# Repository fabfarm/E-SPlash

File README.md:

# FabLab Irrigation System

## Design

C++ for a Microprocessor that includes an embedded http server.

The http server displays controls for N zones, where each zone has:

- turn on time
- turn on duration

```
Valve1 \
Valve2  --- Microprocessor <==> Web Interface  
ValveN /
```

## Web server methods

| **Endpoint** | **Purpose**       |
|--------------|-------------------|
| /getData     | returns json      |
| /updateData  | gets updated json |

## Core Logic

1) start with our json object.
2) we get new data (temp/humidit/y/relay status)
3) update the json object
4) serialize ==> json
5) return json to html

**State Problem**  
When the microcontroller loses power, we lose state. We therefore need to persist settings to disk.

- Settings are *read* from disk on startup
- Settings are *saved* each time a user changes settings in the web ui
- Settings are kept in memory and we check against them

Psuedo code:
```
Startup: 
  - read json to doc obj
  - init wifi
  - init http server

/getData
  - serialize doc obj to Json
  - return Json to caller
  - no logic

/updateData 
  - take incoming Json and save it to disk
  - arduinoJson magically serializes incoming request to our doc object for free
  - no logic 

Loop (no disk i/o):
  - examine current state of in memory doc object and take action
```

## Data format

```json
{
    "data": {
        "currentTime": "Tuesday, June 23 2020 11:54:16",
        "temperature": "29.90",
        "humidity": "51.00",
        "override": 0,
        "ssid": "myssid",
        "pass": "my password"
    },
    "relays": [
        {
            "name": "Fruit Tree",
            "pin": 25,
            "isRunning": 1,
            "isEnabled": 0,
            "times": [
                {
                    "startTime": "03:00",
                    "duration": "0"
                }
            ]
        },
        {
            "name": "Vegie Garden",
            "pin": 26,
            "isRunning": 1,
            "isEnabled": 0,
            "status": 1,
            "times": [
                {
                    "startTime": "12:00",
                    "duration": "0"
                },
                {
                    "startTime": "12:30",
                    "duration": "0"
                }
            ]
        },
        {
            "name": "Cypress Hill",
            "pin": 33,
            "isRunning": 1,
            "isEnabled": 0,
            "status": 1,
            "times": [
                {
                    "startTime": "12:45",
                    "duration": "0"
                },
                {
                    "startTime": "10:00",
                    "duration": "0"
                },
                {
                    "startTime": "16:45",
                    "duration": "0"
                }
            ]
        }
    ]
}

```

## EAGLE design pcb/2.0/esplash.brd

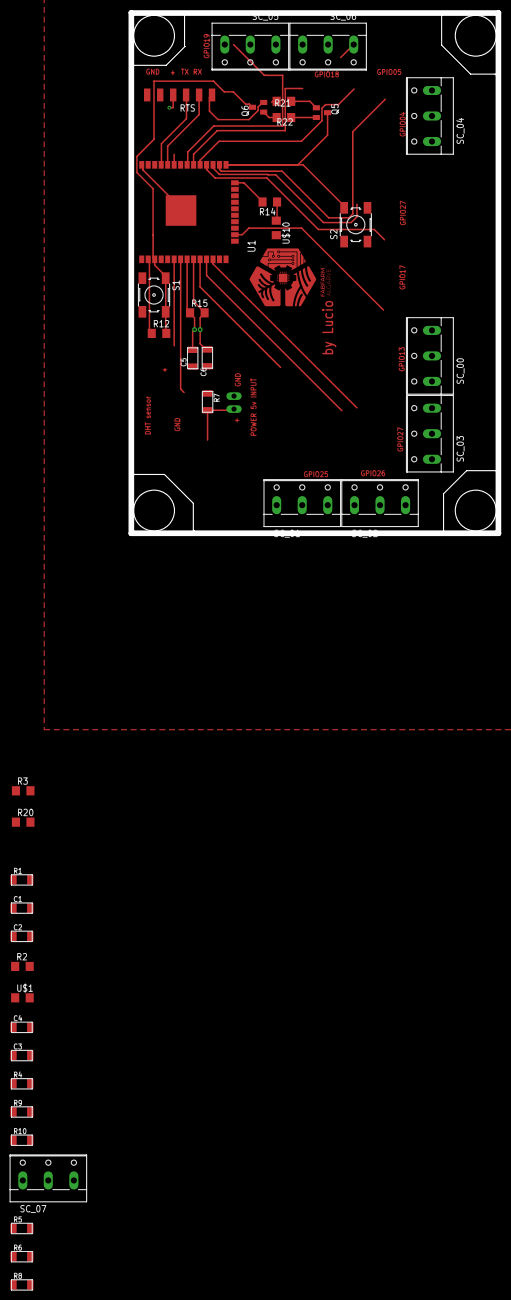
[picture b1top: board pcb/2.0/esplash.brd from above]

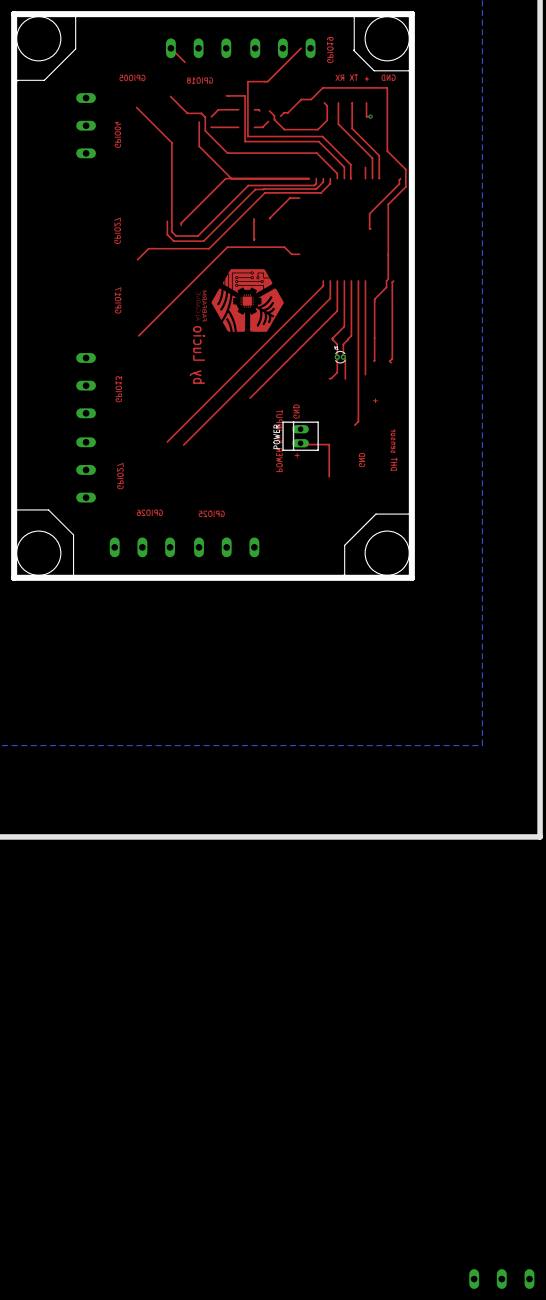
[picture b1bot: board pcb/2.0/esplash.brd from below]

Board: 2 copper layers, 72.0 x 102.0 mm, 40 parts (2 on the bottom side), 31 nets.

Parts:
C1: 10uF; C1206FAB
C2: 100nF; C1206FAB
C3, C4: 1uF; C1206FAB
C5, C6: 15pf; C1206FAB
POWER: 22-23-2021
Q5, Q6: BCX70SMD; SOT23
R1, R6, R8: 10Kohm; R1206FAB
R2, R14: 100ohm; R1206
R3, R20: 50 ohm; R1206
R4: 100Kohm; R1206FAB
R5: 4.9Kohm; R1206FAB
R7: 49.9Kohm; R1206FAB
R9: 50Kohm; R1206FAB
R10: 5Kohm; R1206FAB
R12, R21, R22: 10k; R1206
R15: 5M; R1206
RTS: FTDI-SMD-HEADER; 1X06SMD
S1: Reset; 6MM_SWITCH
S2: GPIO0 Button; 6MM_SWITCH
SC_00, SC_01, SC_02, SC_03, SC_04, SC_05, SC_06, SC_07: SC; W237-103
U1: ESP-WROOM-32
U$1, U$10: LED; LED1206
Y1: ECS-.327-12.5-13X; XTAL_ECS-.327-12.5-13X

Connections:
3V3: C1.2, C2.1, C3.1, R2.2, R12.1, U1.2
32K_XN: C6.2, R15.2, U1.9, Y1.1
32K_XP: C5.2, R15.1, U1.8, Y1.2
BUT_CHIP_LO: R20.1, S1.3, S1.4
BUT_IO0_LO: R3.1, S2.3, S2.4
CHIP_PU: C4.1, Q6.3, R12.2, S1.1, S1.2, U1.3
DTR: Q5.2, R22.2
GND: C1.1, C2.2, C3.2, C4.2, C5.1, C6.1, POWER.2, R1.1, R3.2, R20.2, RTS.1, SC_00.1, SC_01.1, SC_02.1, SC_03.1, SC_04.1, SC_05.1, SC_06.1, SC_07.1, U1.1, U1.15, U1.38, U1.GND, U$1.2, U$10.2
GPIO0: Q5.3, S2.1, S2.2, U1.25
GPIO1/TXD0: RTS.4, U1.35
GPIO02: R14.2, U1.24
GPIO3/RXD0: RTS.5, U1.34
GPIO4/POWER_VOLT_IN: R1.2, R10.1, U1.26
GPIO12/BATT_IN_7: SC_06.3, U1.14
GPIO13/BATT_IN_8: SC_07.3, U1.16
GPIO14/BATT_IN_6: SC_05.3, U1.13
GPIO25/BATT_IN_3: SC_02.3, U1.10
GPIO26/BATT_IN_4: SC_03.3, U1.11
GPIO27/BATT_IN_5: SC_04.3, U1.12
GPIO34/BATT_IN_1: SC_00.3, U1.6
GPIO35/BATT_IN_2: SC_01.3, U1.7
unnamed: R2.1, U$1.1
unnamed: R4.2, R7.1, R9.2
unnamed: R4.1, R9.1, R10.2
unnamed: R5.1, R6.2
unnamed: R6.1, R8.2
unnamed: R14.1, U$10.1
unnamed: Q5.1, R21.1
unnamed: Q6.1, R22.1
RTS: Q6.2, R21.2, RTS.6
VCC: POWER.1, R7.2, RTS.3, SC_00.2, SC_01.2, SC_02.2, SC_03.2, SC_04.2, SC_05.2, SC_06.2, SC_07.2

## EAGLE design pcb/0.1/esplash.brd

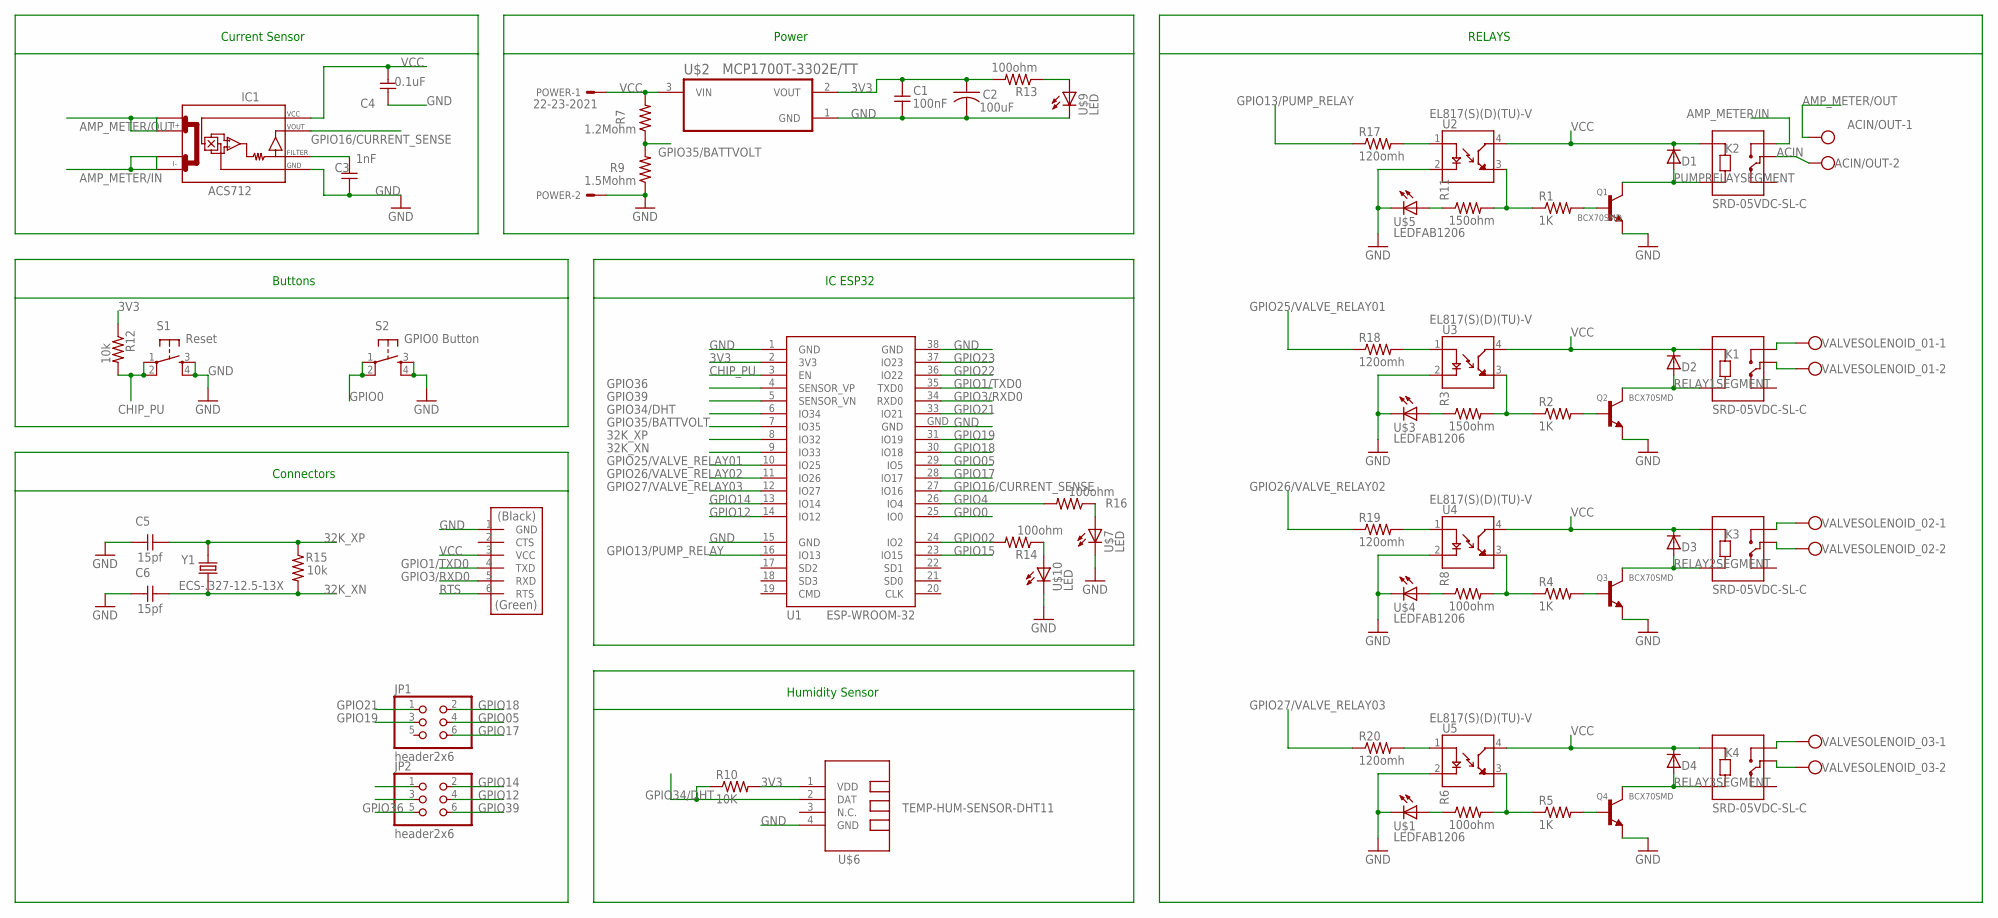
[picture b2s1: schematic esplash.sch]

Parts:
ACIN/OUT: W237-102
C1: 100nF; C1206FAB
C2: 100uF; C1206FAB
C3: 1nF; C1206FAB
C4: 0.1uF; C1206FAB
C5, C6: 15pf; C1206FAB
D1, D2, D3, D4: DIODESOD123; SOD123
IC1: ACS712; SO08
JP1, JP2: header2x6; 2X03
K1, K2, K3, K4: SRD-05VDC-SL-C; RELAY_SRD-05VDC-SL-C
POWER: 22-23-2021
Q1, Q2, Q3, Q4: BCX70SMD; SOT23
R1, R2, R4, R5: 1K; R1206FAB
R3, R11: 150ohm; R1206FAB
R6, R8: 100ohm; R1206FAB
R7: 1.2Mohm; R1206FAB
R9: 1.5Mohm; R1206FAB
R10: 10K; R1206FAB
R12, R15: 10k; R1206
R13, R14, R16: 100ohm; R1206
R17, R18, R19, R20: 120omh; R1206FAB
RTS: FTDI-SMD-HEADER; 1X06SMD
S1: Reset; 6MM_SWITCH
S2: GPIO0 Button; 6MM_SWITCH
U1: ESP-WROOM-32
U2, U3, U4, U5: EL817(S)(D)(TU)-V; SOIC254P1030X460-4N
U$1, U$3, U$4, U$5: LEDFAB1206; LED1206FAB
U$2: MCP1700T-3302E/TT; SOT95P237X112-3N
U$6: TEMP-HUM-SENSOR-DHT11
U$7, U$9, U$10: LED; LED1206
VALVESOLENOID_01, VALVESOLENOID_02, VALVESOLENOID_03: W237-102
Y1: ECS-.327-12.5-13X; XTAL_ECS-.327-12.5-13X

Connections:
3V3: C1.2, C2.1, R10.2, R12.1, R13.2, U1.2 (3V3), U$2.2 (VOUT), U$6.1 (VDD)
32K_XN: C6.2, R15.2, U1.9 (IO33), Y1.1
32K_XP: C5.2, R15.1, U1.8 (IO32), Y1.2
ACIN: ACIN/OUT.2, K2.COM
AMP_METER/IN: IC1.3 (I-_0), IC1.4 (I-_1), K2.NO
AMP_METER/OUT: ACIN/OUT.1, IC1.1 (I+_0), IC1.2 (I+_1)
CHIP_PU: R12.2, S1.1, S1.2 (P1), U1.3 (EN)
DELETE: C3.2, IC1.6 (FILTER)
GND: C1.1, C2.2, C3.1, C4.1, C5.1, C6.1, IC1.5 (GND), POWER.2, Q1.2 (E), Q2.2 (E), Q3.2 (E), Q4.2 (E), R9.1, RTS.1 (GND), S1.3 (S), S1.4 (S1), S2.3 (S), S2.4 (S1), U1.1 (GND), U1.15 (GND), U1.38 (GND), U1.GND, U2.2 (C), U3.2 (C), U4.2 (C), U5.2 (C), U$1.2 (C), U$2.1 (GND), U$3.2 (C), U$4.2 (C), U$5.2 (C), U$6.4 (GND), U$7.2 (C), U$9.2 (C), U$10.2 (C)
GPIO0: S2.1, S2.2 (P1), U1.25 (IO0)
GPIO1/TXD0: RTS.4 (TXD), U1.35 (TXD0)
GPIO02: R14.2, U1.24 (IO2)
GPIO3/RXD0: RTS.5 (RXD), U1.34 (RXD0)
GPIO4: R16.2, U1.26 (IO4)
GPIO05: JP1.4, U1.29 (IO5)
GPIO12: JP2.4, U1.14 (IO12)
GPIO13/PUMP_RELAY: R17.1, U1.16 (IO13)
GPIO14: JP2.2, U1.13 (IO14)
GPIO15: U1.23 (IO15)
GPIO16/CURRENT_SENSE: IC1.7 (VOUT), U1.27 (IO16)
GPIO17: JP1.6, U1.28 (IO17)
GPIO18: JP1.2, U1.30 (IO18)
GPIO19: JP1.3, U1.31 (IO19)
GPIO21: JP1.1, U1.33 (IO21)
GPIO22: U1.36 (IO22)
GPIO23: U1.37 (IO23)
GPIO25/VALVE_RELAY01: R18.1, U1.10 (IO25)
GPIO26/VALVE_RELAY02: R19.1, U1.11 (IO26)
GPIO27/VALVE_RELAY03: R20.1, U1.12 (IO27)
GPIO34/DHT: R10.1, U1.6 (IO34), U$6.2 (DAT)
GPIO35/BATTVOLT: R7.1, R9.2, U1.7 (IO35)
GPIO36: JP2.5, U1.4 (SENSOR_VP)
GPIO39: JP2.6, U1.5 (SENSOR_VN)
unnamed: R1.1, R11.2, U2.3 (ET)
unnamed: K1.COM, VALVESOLENOID_01.2
unnamed: Q2.1 (B), R2.2
unnamed: R11.1, U$5.1 (A)
unnamed: R14.1, U$10.1 (A)
unnamed: K1.NO, VALVESOLENOID_01.1
unnamed: R3.1, U$3.1 (A)
unnamed: R2.1, R3.2, U3.3 (ET)
unnamed: K3.COM, VALVESOLENOID_02.2
unnamed: Q3.1 (B), R4.2
unnamed: R8.1, U$4.1 (A)
unnamed: R4.1, R8.2, U4.3 (ET)
unnamed: K3.NO, VALVESOLENOID_02.1
unnamed: K4.COM, VALVESOLENOID_03.2
unnamed: Q4.1 (B), R5.2
unnamed: R6.1, U$1.1 (A)
unnamed: R5.1, R6.2, U5.3 (ET)
unnamed: K4.NO, VALVESOLENOID_03.1
unnamed: R13.1, U$9.1 (A)
unnamed: R16.1, U$7.1 (A)
unnamed: R17.2, U2.1 (A)
unnamed: R18.2, U3.1 (A)
unnamed: R19.2, U4.1 (A)
unnamed: R20.2, U5.1 (A)
unnamed: Q1.1 (B), R1.2
PUMPRELAYSEGMENT: D1.ANODE (A), K2.A2, Q1.3 (C)
RELAY1SEGMENT: D2.ANODE (A), K1.A2, Q2.3 (C)
RELAY2SEGMENT: D3.ANODE (A), K3.A2, Q3.3 (C)
RELAY3SEGMENT: D4.ANODE (A), K4.A2, Q4.3 (C)
RTS: RTS.6 (RTS)
VCC: C4.2, D1.CATHODE (C), D2.CATHODE (C), D3.CATHODE (C), D4.CATHODE (C), IC1.8 (VCC), K1.A1, K2.A1, K3.A1, K4.A1, POWER.1, R7.2, RTS.3 (VCC), U2.4 (CT), U3.4 (CT), U4.4 (CT), U5.4 (CT), U$2.3 (VIN)

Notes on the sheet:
RELAYS
Power
IC ESP32
Humidity Sensor
Current Sensor
Buttons
Connectors

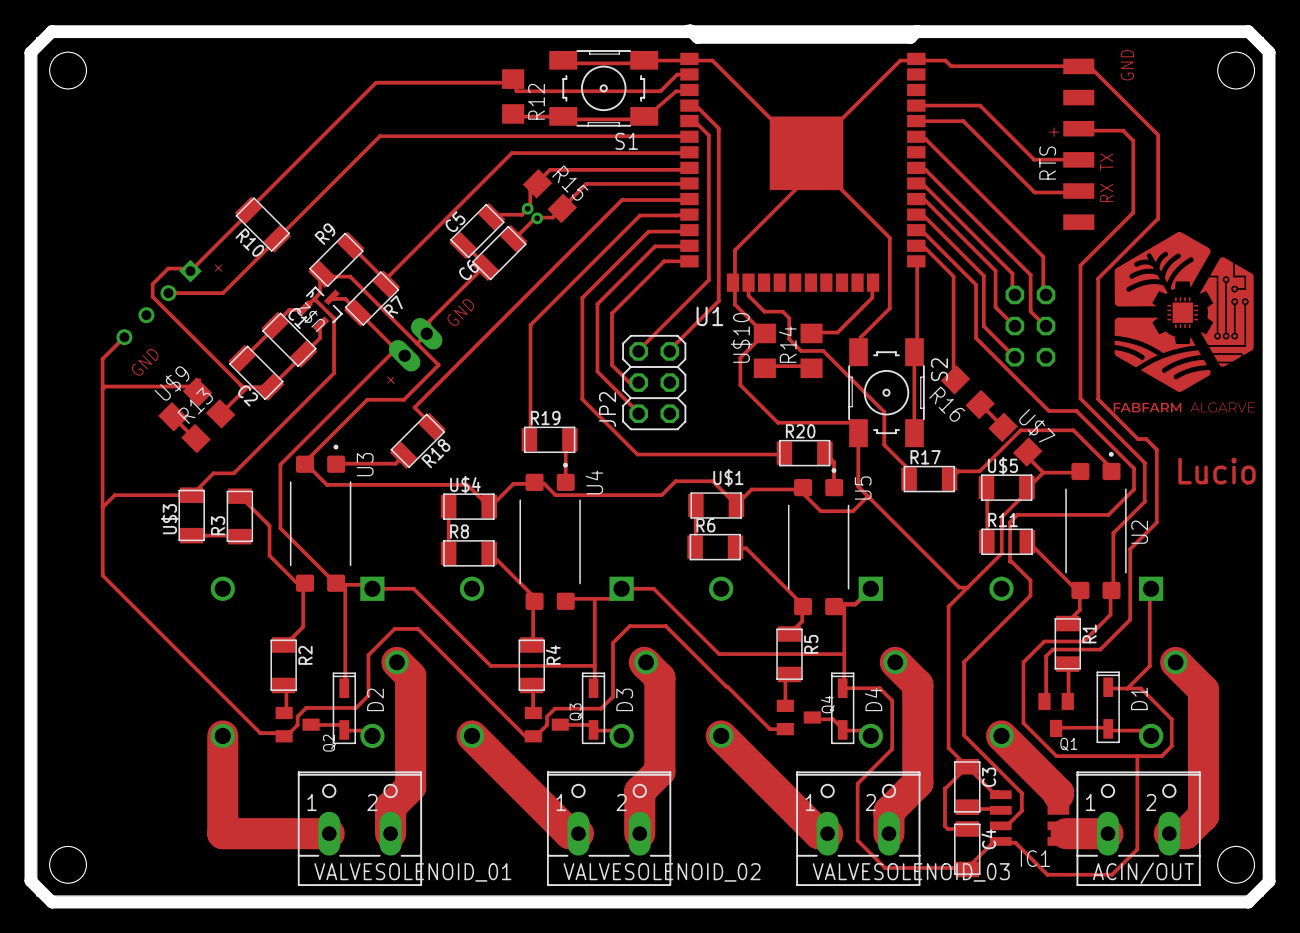
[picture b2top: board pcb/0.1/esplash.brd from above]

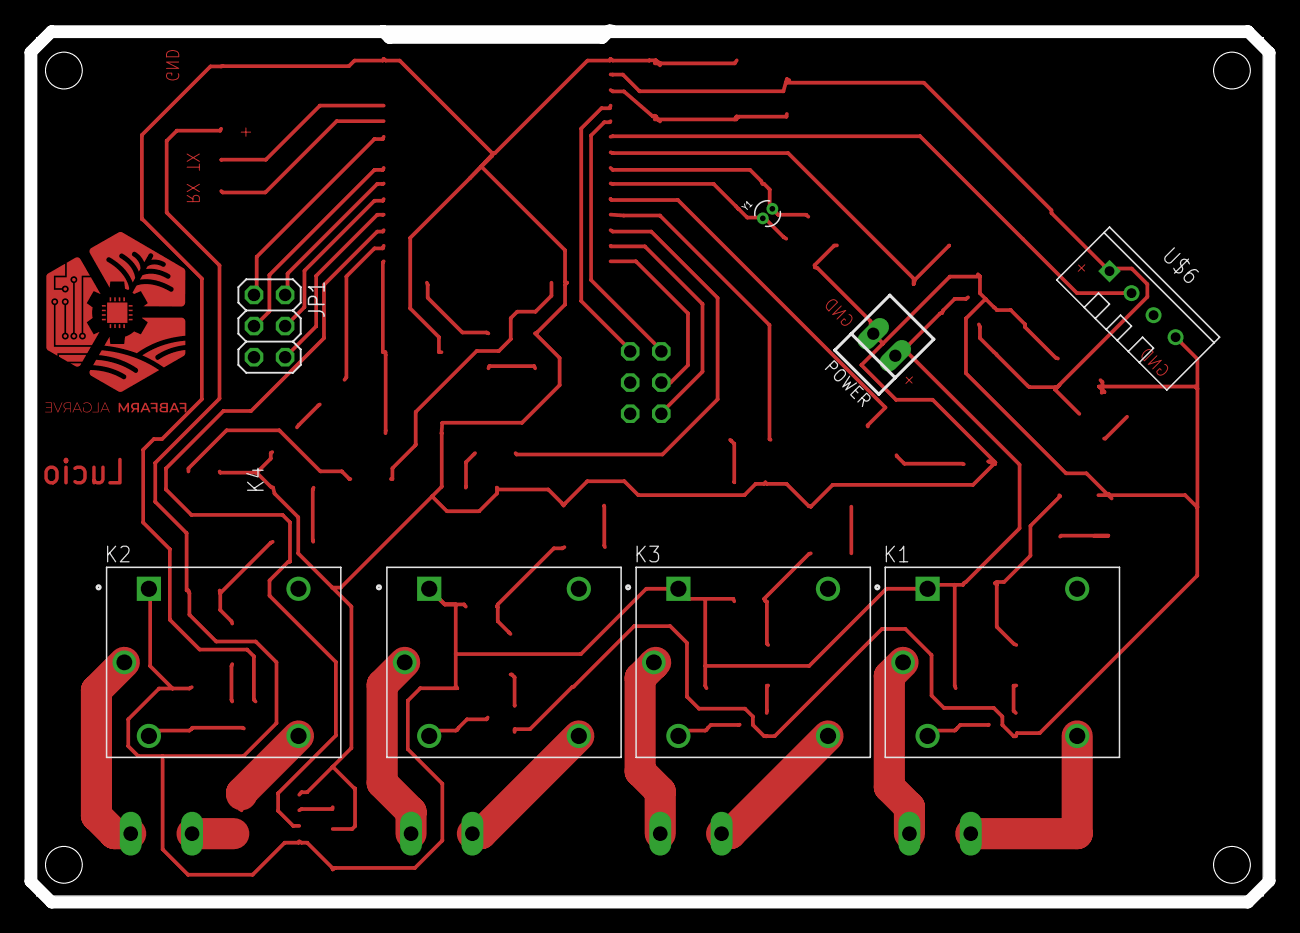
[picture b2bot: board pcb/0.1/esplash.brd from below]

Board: 2 copper layers, 101.0 x 71.0 mm, 64 parts (8 on the bottom side), 60 nets.

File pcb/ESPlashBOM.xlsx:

Part | Value | Device | Package | Description | ARROW_AMERICAS-PURCHASE-URL | AVAILABILITY | DESCRIPTION.1 | DIGIKEY-PURCHASE-URL | MF | MOUSER-PURCHASE-URL | MP | MPN | OC_FARNELL | OC_NEWARK | PACKAGE.1 | POPULARITY | PRICE | Column1
POWER | 22-23-2021 | 22-23-2021 | 22-23-2021 | .100 (2.54mm) Center Header - 2 Pin" |  |  |  |  | MOLEX |  |  | 22-23-2021 | 1462926 | 25C3832 |  | 40
S2 | GPIO0 Button | 6MM_SWITCH6MM_SWITCH | 6MM_SWITCH | OMRON SWITCH
S1 | Reset | 6MM_SWITCH6MM_SWITCH | 6MM_SWITCH | OMRON SWITCH
IC1 | ACS712 | ACS712 | SO08
Q1 | BCX70SMD | BCX70SMD | SOT23 | NPN TRANSISTOR |  |  |  |  |  |  |  |  |  |  |  | 0
Q2 | BCX70SMD | BCX70SMD | SOT23 | NPN TRANSISTOR |  |  |  |  |  |  |  |  |  |  |  | 0
Q3 | BCX70SMD | BCX70SMD | SOT23 | NPN TRANSISTOR |  |  |  |  |  |  |  |  |  |  |  | 0
Q4 | BCX70SMD | BCX70SMD | SOT23 | NPN TRANSISTOR |  |  |  |  |  |  |  |  |  |  |  | 0
C4 | 0.1uF | CAP-UNPOLARIZEDFAB | C1206FAB
C1 | 100nF | CAP-UNPOLARIZEDFAB | C1206FAB
C5 | 15pf | CAP-UNPOLARIZEDFAB | C1206FAB
C6 | 15pf | CAP-UNPOLARIZEDFAB | C1206FAB
C3 | 1nF | CAP-UNPOLARIZEDFAB | C1206FAB
C2 | 100uF | CAP-US1206FAB | C1206FAB
D1 |  | DIODESOD123 | SOD123 | DIODE
D2 |  | DIODESOD123 | SOD123 | DIODE
D3 |  | DIODESOD123 | SOD123 | DIODE
D4 |  | DIODESOD123 | SOD123 | DIODE
Y1 | ECS-.327-12.5-13X | ECS-.327-12.5-13X | XTAL_ECS-.327-12.5-13X | Crystal Cylindrical Can, Radial |  | Unavailable | 32.768kHz Â±20ppm Crystal 12.5pF 35 kOhms Cylindrical Can, Radial |  | ECS Inc. |  | ECS-.327-12.5-13X |  |  |  | Cylindrical Can Radial ECS International |  | None
U2 | EL817(S)(D)(TU)-V | EL817(S)(D)(TU)-V | SOIC254P1030X460-4N | Optocoupler DC-IN 1-CH Transistor DC-OUT 4-Pin PDIP Tube |  | Unavailable | Optoisolator Transistor Output 5000Vrms 1 Channel 4-SMD |  | Everlight Electronics |  | EL817(S)(D)(TU)-V |  |  |  | SMD-4 Everlight |  | None
U3 | EL817(S)(D)(TU)-V | EL817(S)(D)(TU)-V | SOIC254P1030X460-4N | Optocoupler DC-IN 1-CH Transistor DC-OUT 4-Pin PDIP Tube |  | Unavailable | Optoisolator Transistor Output 5000Vrms 1 Channel 4-SMD |  | Everlight Electronics |  | EL817(S)(D)(TU)-V |  |  |  | SMD-4 Everlight |  | None
U4 | EL817(S)(D)(TU)-V | EL817(S)(D)(TU)-V | SOIC254P1030X460-4N | Optocoupler DC-IN 1-CH Transistor DC-OUT 4-Pin PDIP Tube |  | Unavailable | Optoisolator Transistor Output 5000Vrms 1 Channel 4-SMD |  | Everlight Electronics |  | EL817(S)(D)(TU)-V |  |  |  | SMD-4 Everlight |  | None
U5 | EL817(S)(D)(TU)-V | EL817(S)(D)(TU)-V | SOIC254P1030X460-4N | Optocoupler DC-IN 1-CH Transistor DC-OUT 4-Pin PDIP Tube |  | Unavailable | Optoisolator Transistor Output 5000Vrms 1 Channel 4-SMD |  | Everlight Electronics |  | EL817(S)(D)(TU)-V |  |  |  | SMD-4 Everlight |  | None
U1 | ESP-WROOM-32 | ESP-WROOM-32 | ESP-WROOM-32 | Espressif Systems ESP-WROOM-32
RTS | FTDI-SMD-HEADER | FTDI-SMD-HEADER | 1X06SMD
U$7 | LED | LED | LED1206 | LED
U$9 | LED | LED | LED1206 | LED
U$10 | LED | LED | LED1206 | LED
U$1 | LEDFAB1206 | LEDFAB1206 | LED1206FAB | LED
U$3 | LEDFAB1206 | LEDFAB1206 | LED1206FAB | LED
U$4 | LEDFAB1206 | LEDFAB1206 | LED1206FAB | LED
U$5 | LEDFAB1206 | LEDFAB1206 | LED1206FAB | LED
U$2 | MCP1700T-3302E/TT | MCP1700T-3302E/TT | SOT95P237X112-3N |  | https://snapeda.com/shop?store=Arrow+Americas&id=4791194 | Unavailable | IC REG LINEAR 3.3V 250MA SOT23-3 | https://snapeda.com/shop?store=DigiKey&id=4791194 | Microchip Technology | https://snapeda.com/shop?store=Mouser&id=4791194 | MCP1700T-3302E/TT |  |  |  | None |  | None
JP1 | header2x6 | PINHD-2X3 | 2X03 | PIN HEADER |  |  |  |  |  |  |  |  |  |  |  | 62
JP2 | header2x6 | PINHD-2X3 | 2X03 | PIN HEADER |  |  |  |  |  |  |  |  |  |  |  | 62
R13 | 100ohm | RES-US1206 | R1206 | Resistor (US Symbol)
R14 | 100ohm | RES-US1206 | R1206 | Resistor (US Symbol)
R16 | 100ohm | RES-US1206 | R1206 | Resistor (US Symbol)
R12 | 10k | RES-US1206 | R1206 | Resistor (US Symbol)
R15 | 10k | RES-US1206 | R1206 | Resistor (US Symbol)
R7 | 1.2Mohm | RES-US1206FAB | R1206FAB | Resistor (US Symbol)
R9 | 1.5Mohm | RES-US1206FAB | R1206FAB | Resistor (US Symbol)
R3 | 100ohm | RES-US1206FAB | R1206FAB | Resistor (US Symbol)
R6 | 100ohm | RES-US1206FAB | R1206FAB | Resistor (US Symbol)
R8 | 100ohm | RES-US1206FAB | R1206FAB | Resistor (US Symbol)
R11 | 100ohm | RES-US1206FAB | R1206FAB | Resistor (US Symbol)
R10 | 10K | RES-US1206FAB | R1206FAB | Resistor (US Symbol)
R1 | 1K | RES-US1206FAB | R1206FAB | Resistor (US Symbol)
R2 | 1K | RES-US1206FAB | R1206FAB | Resistor (US Symbol)
R4 | 1K | RES-US1206FAB | R1206FAB | Resistor (US Symbol)
R5 | 1K | RES-US1206FAB | R1206FAB | Resistor (US Symbol)
K1 | SRD-05VDC-SL-C | SRD-05VDC-SL-C | RELAY_SRD-05VDC-SL-C | 5V Trigger Relay Module For Arduino And Raspberry Pi 5V Trigger Relay Module Fo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 |  | Unavailable | 5V Trigger Relay Module For Arduino And Raspberry Pi 5V Trigger Relay Module Fo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 |  | Songle Relay |  | SRD-05VDC-SL-C |  |  |  | None |  | None
K2 | SRD-05VDC-SL-C | SRD-05VDC-SL-C | RELAY_SRD-05VDC-SL-C | 5V Trigger Relay Module For Arduino And Raspberry Pi 5V Trigger Relay Module Fo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 |  | Unavailable | 5V Trigger Relay Module For Arduino And Raspberry Pi 5V Trigger Relay Module Fo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 |  | Songle Relay |  | SRD-05VDC-SL-C |  |  |  | None |  | None
K3 | SRD-05VDC-SL-C | SRD-05VDC-SL-C | RELAY_SRD-05VDC-SL-C | 5V Trigger Relay Module For Arduino And Raspberry Pi 5V Trigger Relay Module Fo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 |  | Unavailable | 5V Trigger Relay Module For Arduino And Raspberry Pi 5V Trigger Relay Module Fo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 |  | Songle Relay |  | SRD-05VDC-SL-C |  |  |  | None |  | None
K4 | SRD-05VDC-SL-C | SRD-05VDC-SL-C | RELAY_SRD-05VDC-SL-C | 5V Trigger Relay Module For Arduino And Raspberry Pi 5V Trigger Relay Module Fo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 |  | Unavailable | 5V Trigger Relay Module For Arduino And Raspberry Pi 5V Trigger Relay Module Fo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 |  | Songle Relay |  | SRD-05VDC-SL-C |  |  |  | None |  | None
U$6 | TEMP-HUM-SENSOR-DHT11 | TEMP-HUM-SENSOR-DHT11 | TEMP-HUM-SENSOR-DHT11 | DHT11 - digital humidity & temperature sensor
ACIN/OUT |  | W237-102 | W237-102 | WAGO SCREW CLAMP |  |  |  |  |  |  |  | 237-102 | unknown | 70K9898
VALVESOLENOID_01 |  | W237-102 | W237-102 | WAGO SCREW CLAMP |  |  |  |  |  |  |  | 237-102 | unknown | 70K9898
VALVESOLENOID_02 |  | W237-102 | W237-102 | WAGO SCREW CLAMP |  |  |  |  |  |  |  | 237-102 | unknown | 70K9898
VALVESOLENOID_03 |  | W237-102 | W237-102 | WAGO SCREW CLAMP |  |  |  |  |  |  |  | 237-102 | unknown | 70K9898

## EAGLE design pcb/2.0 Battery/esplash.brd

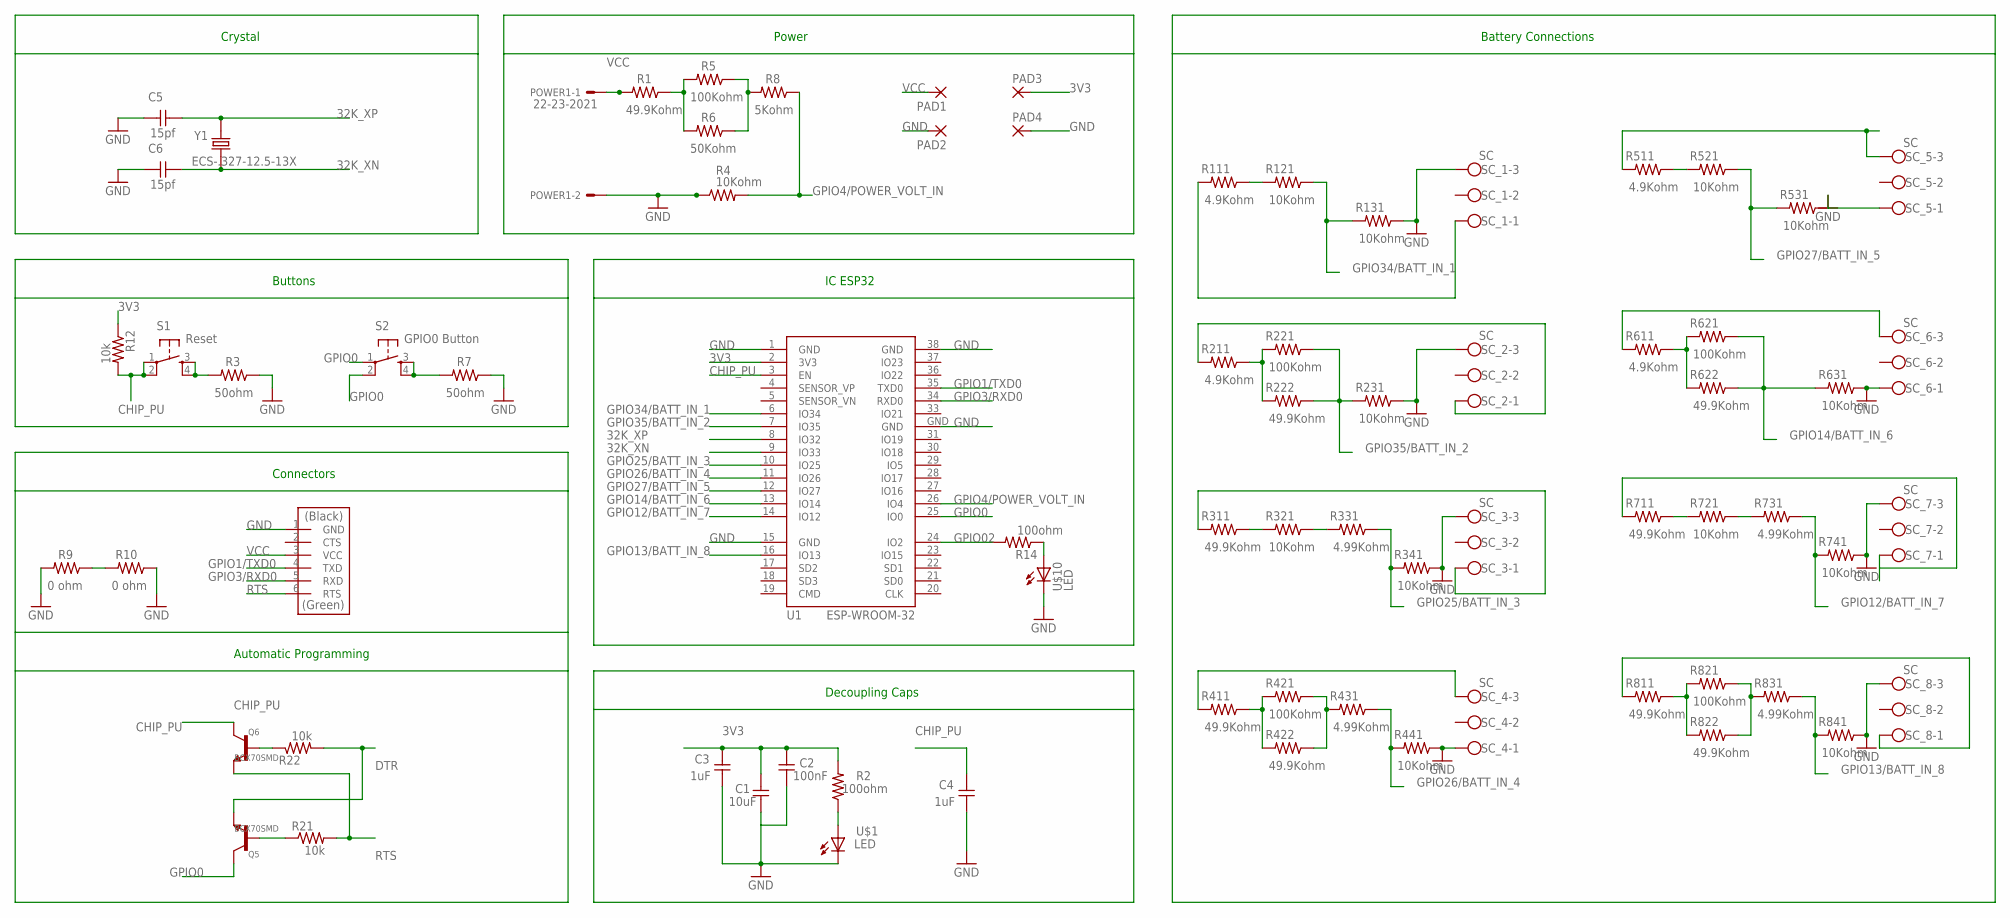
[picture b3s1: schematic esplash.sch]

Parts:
C1: 10uF; C1206FAB
C2: 100nF; C1206FAB
C3, C4: 1uF; C1206FAB
C5, C6: 15pf; C1206FAB
PAD1, PAD2, PAD3, PAD4: 2,15/1,0
POWER1: 22-23-2021
Q5, Q6: BCX70SMD; SOT23
R1, R222, R311, R411, R422, R622, R711, R811, R822: 49.9Kohm; R1206FAB
R2, R14: 100ohm; R1206
R3, R7: 50ohm; R1206FAB
R4, R121, R131, R231, R321, R341, R441, R521, R531, R631, R721, R741, R841: 10Kohm; R1206FAB
R5, R221, R421, R621, R821: 100Kohm; R1206FAB
R6: 50Kohm; R1206FAB
R8: 5Kohm; R1206FAB
R9, R10: 0 ohm; R1206FAB
R12, R21, R22: 10k; R1206
R111, R211, R511, R611: 4.9Kohm; R1206FAB
R331, R431, R731, R831: 4.99Kohm; R1206FAB
RTS: FTDI-SMD-HEADER; 1X06SMD
S1: Reset; 6MM_SWITCH
S2: GPIO0 Button; 6MM_SWITCH
SC_1, SC_2, SC_3, SC_4, SC_5, SC_6, SC_7, SC_8: SC; W237-103
U1: ESP-WROOM-32
U$1, U$10: LED; LED1206
Y1: ECS-.327-12.5-13X; XTAL_ECS-.327-12.5-13X

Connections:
3V3: C1.2, C2.1, C3.1, PAD3.1, R2.2, R12.1, U1.2 (3V3)
32K_XN: C6.2, U1.9 (IO33), Y1.1
32K_XP: C5.2, U1.8 (IO32), Y1.2
CHIP_PU: C4.1, Q6.3 (C), R12.2, S1.1, S1.2 (P1), U1.3 (EN)
DTR: Q5.2 (E), R22.2
GND: C1.1, C2.2, C3.2, C4.2, C5.1, C6.1, PAD2.1, PAD4.1, POWER1.2, R3.1, R4.1, R7.1, R9.2, R10.1, R131.1, R231.1, R341.1, R441.1, R531.1, R631.1, R741.1, R841.1, RTS.1 (GND), SC_1.3, SC_2.3, SC_3.3, SC_4.1, SC_5.1, SC_6.1, SC_7.3, SC_8.3, U1.1 (GND), U1.15 (GND), U1.38 (GND), U1.GND, U$1.2 (C), U$10.2 (C)
GPIO0: Q5.3 (C), S2.1, S2.2 (P1), U1.25 (IO0)
GPIO1/TXD0: RTS.4 (TXD), U1.35 (TXD0)
GPIO02: R14.2, U1.24 (IO2)
GPIO3/RXD0: RTS.5 (RXD), U1.34 (RXD0)
GPIO4/POWER_VOLT_IN: R4.2, R8.1, U1.26 (IO4)
GPIO12/BATT_IN_7: R731.1, R741.2, U1.14 (IO12)
GPIO13/BATT_IN_8: R831.1, R841.2, U1.16 (IO13)
GPIO14/BATT_IN_6: R621.1, R622.1, R631.2, U1.13 (IO14)
GPIO25/BATT_IN_3: R331.1, R341.2, U1.10 (IO25)
GPIO26/BATT_IN_4: R431.1, R441.2, U1.11 (IO26)
GPIO27/BATT_IN_5: R521.1, R531.2, U1.12 (IO27)
GPIO34/BATT_IN_1: R121.1, R131.2, U1.6 (IO34)
GPIO35/BATT_IN_2: R221.1, R222.1, R231.2, U1.7 (IO35)
unnamed: R1.1, R5.2, R6.2
unnamed: R3.2, S1.3 (S), S1.4 (S1)
unnamed: R111.1, R121.2
unnamed: R14.1, U$10.1 (A)
unnamed: R111.2, SC_1.1
unnamed: R5.1, R6.1, R8.2
unnamed: R211.2, SC_2.1
unnamed: R611.2, SC_6.3
unnamed: R9.1, R10.2
unnamed: R2.1, U$1.1 (A)
unnamed: R211.1, R221.2, R222.2
unnamed: R7.2, S2.3 (S), S2.4 (S1)
unnamed: R311.2, SC_3.1
unnamed: R311.1, R321.2
unnamed: Q5.1 (B), R21.1
unnamed: R321.1, R331.2
unnamed: R411.2, SC_4.3
unnamed: R411.1, R421.2, R422.2
unnamed: Q6.1 (B), R22.1
unnamed: R421.1, R422.1, R431.2
unnamed: R511.1, R521.2
unnamed: R511.2, SC_5.3
unnamed: R611.1, R621.2, R622.2
unnamed: R711.2, SC_7.1
unnamed: R711.1, R721.2
unnamed: R721.1, R731.2
unnamed: R811.2, SC_8.1
unnamed: R811.1, R821.2, R822.2
unnamed: R821.1, R822.1, R831.2
RTS: Q6.2 (E), R21.2, RTS.6 (RTS)
VCC: PAD1.1, POWER1.1, R1.2, RTS.3 (VCC)

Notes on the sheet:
Power
IC ESP32
Crystal
Buttons
Connectors
Battery Connections
Automatic Programming
Decoupling Caps

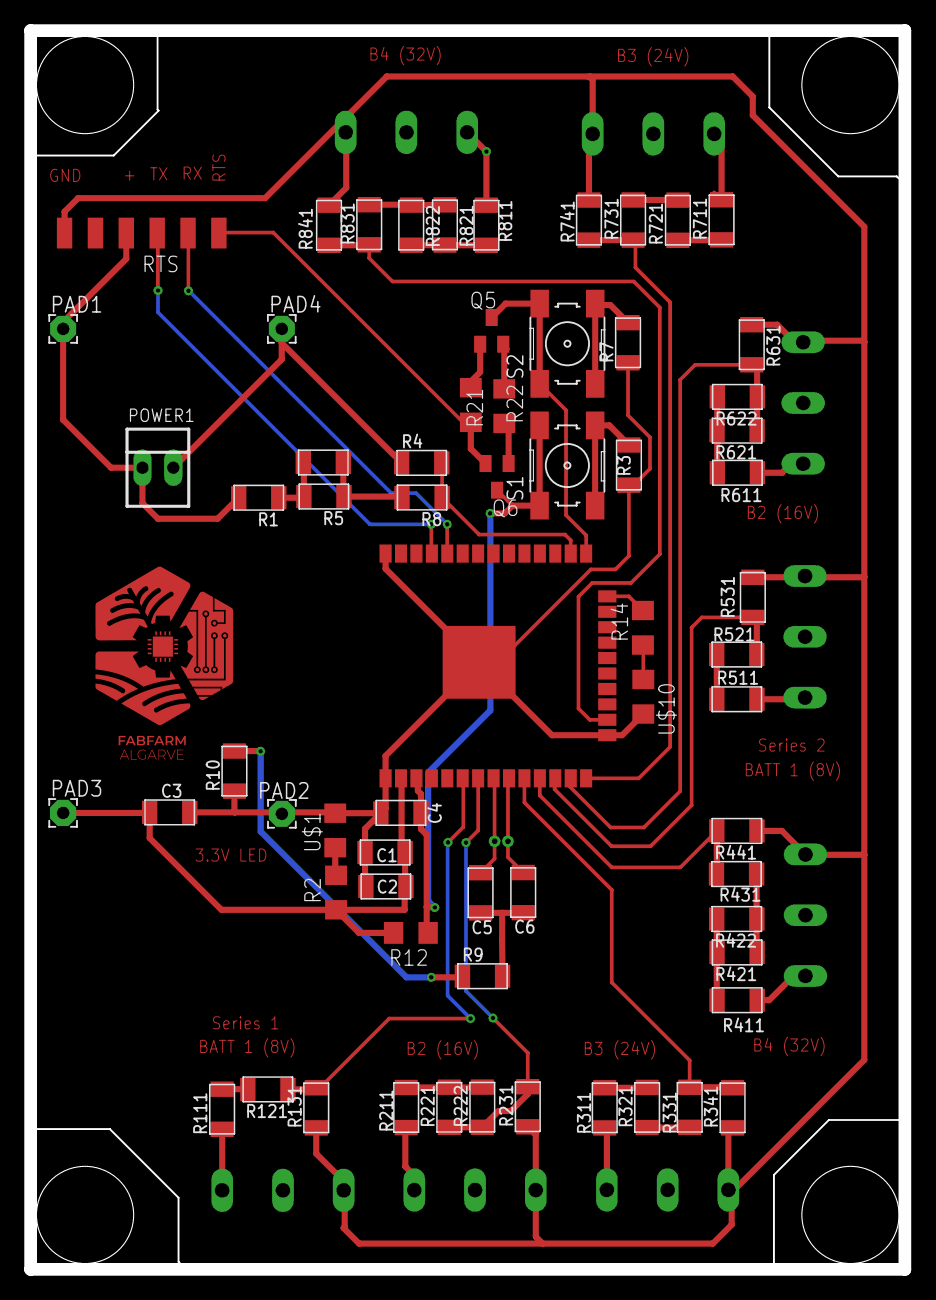
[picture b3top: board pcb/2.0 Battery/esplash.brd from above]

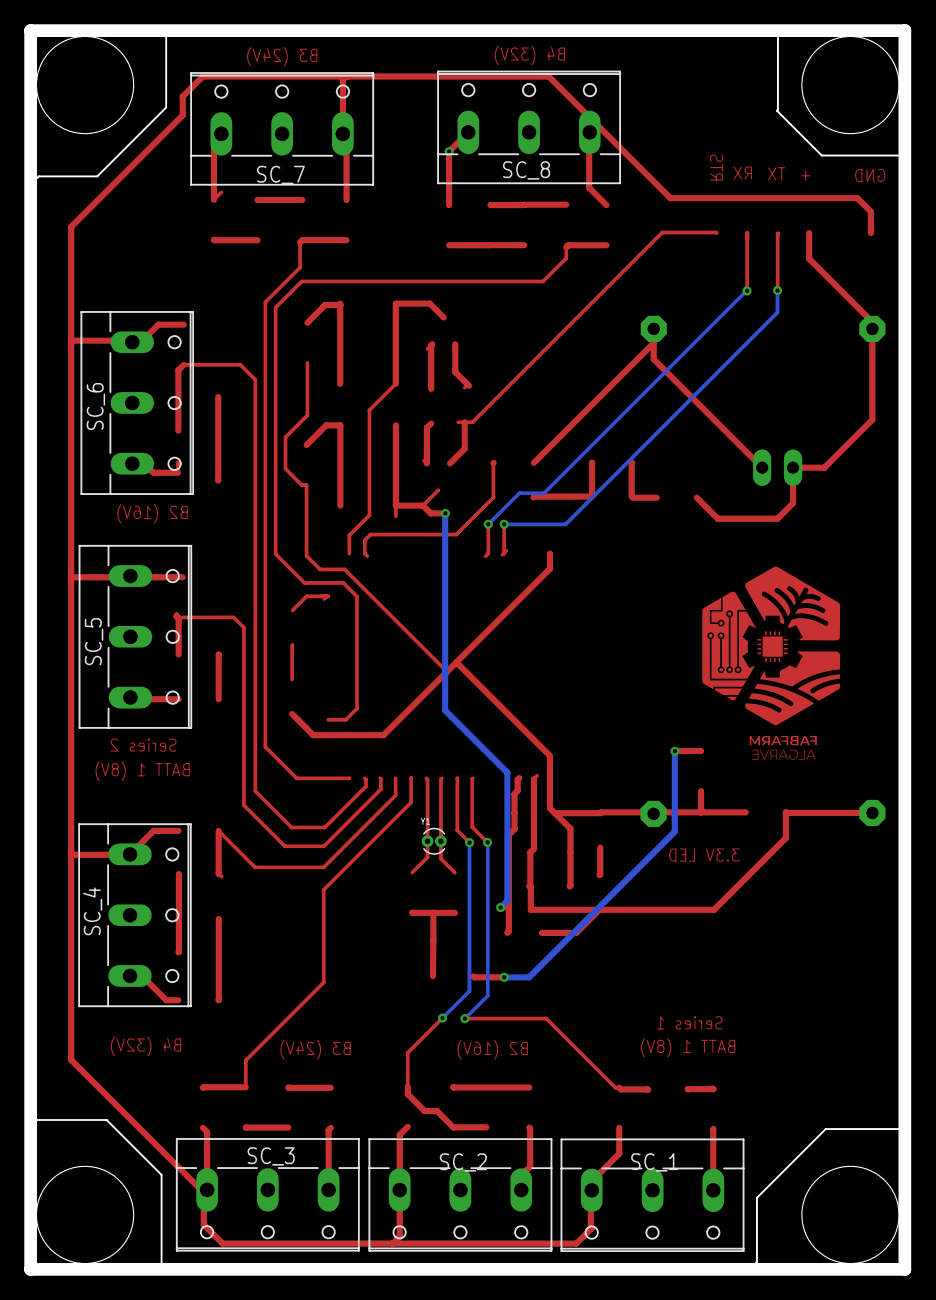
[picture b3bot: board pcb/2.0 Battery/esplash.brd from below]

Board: 2 copper layers, 72.0 x 102.0 mm, 74 parts (9 on the bottom side), 50 nets.

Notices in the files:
parts and their libraries:
esp32: Creative Commons Attribution-ShareAlike 4.0 International
diy-modules: Released under the Creative Commons Attribution 4.0 International License: http://creativecommons.org/licenses/by/4.0
